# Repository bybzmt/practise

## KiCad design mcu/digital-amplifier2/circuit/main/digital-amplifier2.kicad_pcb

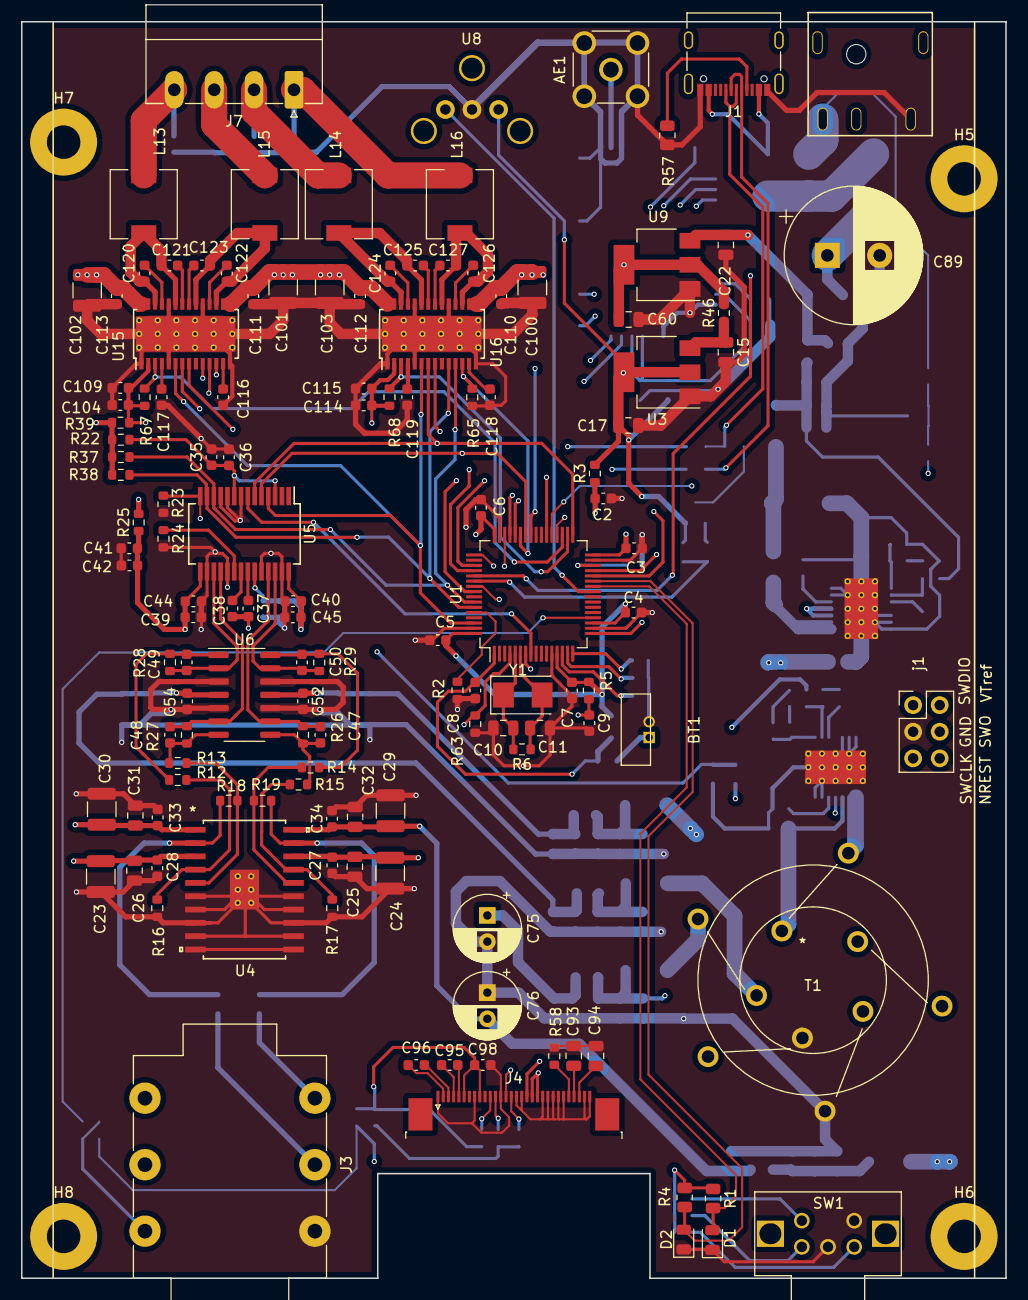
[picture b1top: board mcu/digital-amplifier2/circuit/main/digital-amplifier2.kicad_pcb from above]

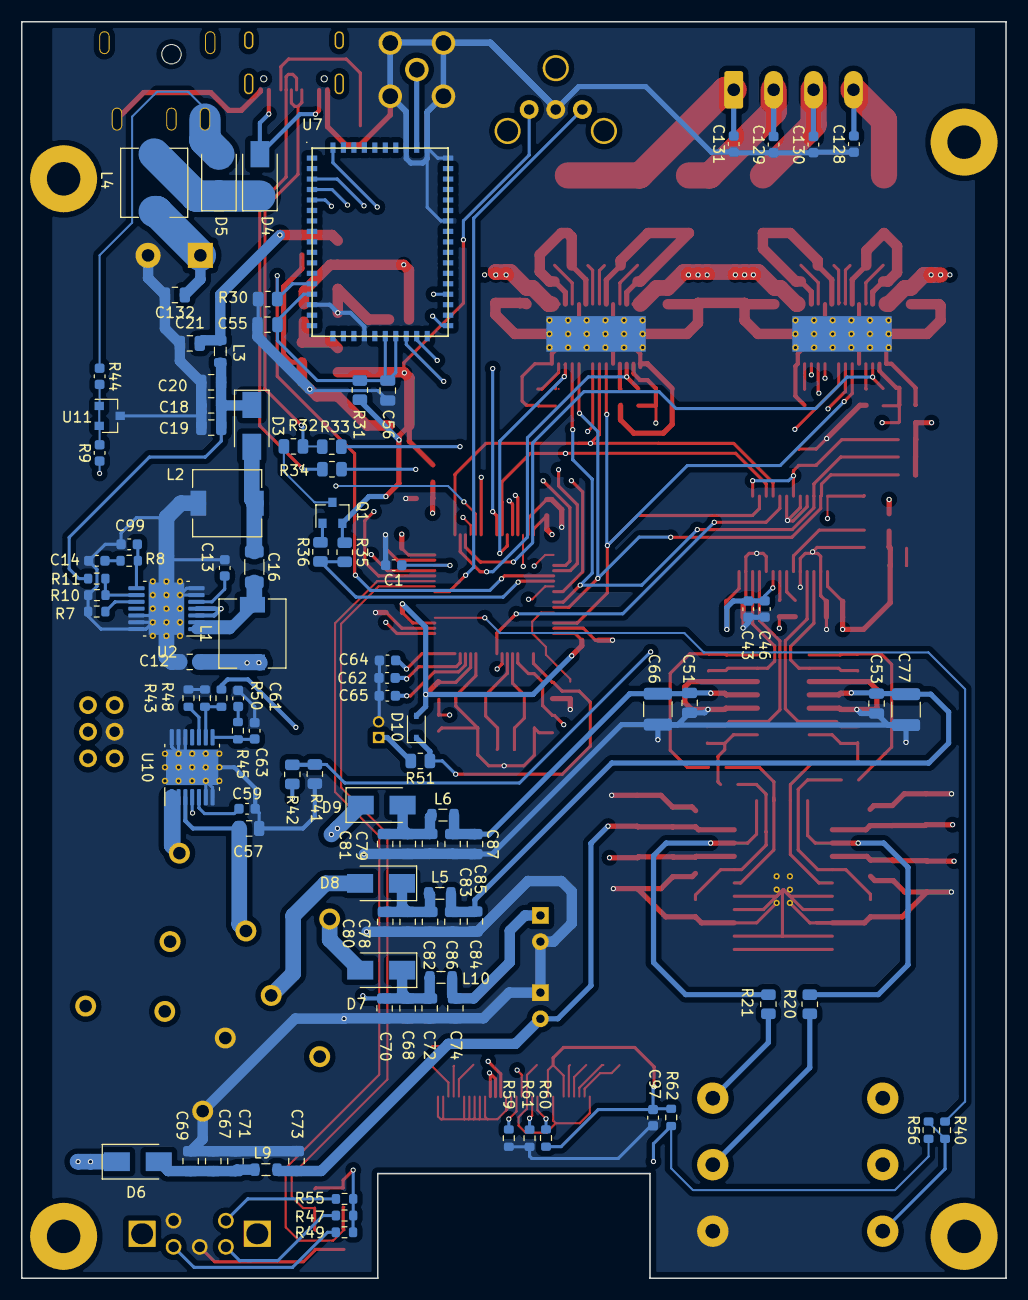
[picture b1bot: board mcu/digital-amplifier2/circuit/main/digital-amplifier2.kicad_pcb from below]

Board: 4 copper layers, 94.0 x 120.0 mm, 237 parts (101 on the bottom side), 140 nets.

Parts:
AE1: Antenna_Shield; SMA_Molex_73251-2200_Horizontal
BT1: MS621FE-FL11E
C1, C104, C114: 4.7uf; C_0603_1608Metric
C2, C35, C39, C41, C43, C45, C97: 10uf; C_0603_1608Metric
C3, C4, C5, C6, C7, C8, C9, C14, C27, C28, C33, C34, C36, C40, C42, C44, C46, C52, C54, C61, C62, C64, C65, C98, C109, C110, C111, C112, C113, C115: 100nf; C_0603_1608Metric
C10, C11: 12pf; C_0805_2012Metric
C12, C15, C25, C26, C31, C32, C51, C53, C56, C57, C93, C94, C132: 10uf; C_0805_2012Metric
C13, C59: 47nf; C_0603_1608Metric
C16: 2.2uf; C_1206_3216Metric
C17, C60: 1uf; C_0805_2012Metric
C18, C19, C21, C22, C55, C67, C68, C69, C70, C73, C74, C78, C79, C80, C81, C84, C85, C86, C87: 22uf; C_0805_2012Metric
C20, C71, C72, C82, C83: 100nf; C_0805_2012Metric
C23, C24, C29, C30, C66, C77, C100, C101, C102, C103: 47uf; C_1210_3225Metric
C37, C38: 47uf; C_0603_1608Metric
C47, C48, C49, C50: 2.7nf; C_0603_1608Metric
C63, C99: NC; C_0603_1608Metric
C75, C76: 220uf; CP_Radial_D6.3mm_P2.50mm
C89: 2200uf; CP_Radial_D13.0mm_P5.00mm
C95, C96, C116, C117, C118, C119: 1uf; C_0603_1608Metric
C120, C121, C122, C123, C124, C125, C126, C127: 220nf; C_0603_1608Metric
C128, C129, C130, C131: 680nf; C_0603_1608Metric
D1: led1; LED_0805_2012Metric
D2: led2; LED_0805_2012Metric
D3, D4, D5, D6, D7, D8, D9: ss34; D_SMA
D10: SD103AWS; D_SOD-323
H5, H6, H7, H8: m3; MountingHole_3.2mm_M3_Pad
J1: USB_C_Receptacle_USB2.0; USB_C_Receptacle_Palconn_UTC16-G
J2: Barrel_Jack_Switch; DC-044A_5.5-2.1
J3: AudioJack3_Switch; Jack_6.35mm_Neutrik_NMJ6HFD2-AU_Horizontal
J4: 0.96_oled; TE_3-1734839-0_1x30-1MP_P0.5mm_Horizontal
J7: PW_OUT; PhoenixContact_MC_1,5_4-G-3.81_1x04_P3.81mm_Horizontal
L1, L2: 22uh / 0630; L_6.3x6.3_H3
L3, L5, L6, L9, L10: 2.2uh / 0805; L_0805_2012Metric
L4: 4.7uh / 0630; L_6.3x6.3_H3
L13, L14, L15, L16: 10uh; L_6.3x6.3_H3
Q1: s8550; SOT-23
R1, R4, R30, R41, R42: 9.53k; R_0805_2012Metric
R2: 9.53kΩ; R_0603_1608Metric
R3, R22, R25, R39, R46, R62: 0Ω; R_0603_1608Metric
R5, R23, R59, R60, R61, R63, R65: 9.53k; R_0603_1608Metric
R6: 1mΩ; R_0603_1608Metric
R7, R43: 43k; R_0603_1608Metric
R8, R45: 2.37k; R_0603_1608Metric
R9, R44: 10k; C_0603_1608Metric
R10, R12, R13, R14, R15, R16, R17, R18, R19, R26, R27, R28, R29, R48: 1k; R_0603_1608Metric
R11: 5k; R_0603_1608Metric
R20, R21: 39.2Ω; R_0805_2012Metric
R24, R40, R47, R49, R55, R56: 10k; R_0603_1608Metric
R31: 0; R_0805_2012Metric
R32: 1.5k; R_0805_2012Metric
R33, R34: 12Ω; R_0805_2012Metric
R35: 22k; R_0805_2012Metric
R36, R57: 5.1k; R_0805_2012Metric
R37, R38: 4.7k; R_0603_1608Metric
R50: 11k; R_0603_1608Metric
R51: 1k; R_0805_2012Metric
R58: 760k; R_0603_1608Metric
R67: 15k; R_0603_1608Metric
R68: 47k; R_0603_1608Metric
SW1: ec11; ec11_horizontal
T1: Transformer_diy_02; Transformer_10p_22x14
U1: STM32F446RETx; LQFP-64_10x10mm_P0.5mm
U2, U10: TPS55340; HTSSOP-14-1EP_4.4x5mm_P0.65mm_EP3.4x5mm_Mask3x3.1mm_Thermal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
U3: AMS1117-3.3; SOT-223-3_TabPin2
U4: TPA6120A2; TPA6120A2DWP
U5: PCM1792A; SSOP-28_5.3x10.2mm_P0.65mm
U6: OPA4134; SOIC-14_3.9x8.7mm_P1.27mm
U7: SJR-BTM331
U8: DLT11H0; spdif-DLT11H0
U9: AMS1117-5.0; SOT-223-3_TabPin2
U11: TL431DBZ; SOT-23
U15, U16: tas5805m; HTSSOP-28-1EP_4.4x9.7mm_P0.65mm_EP3.4x9.5mm_ThermalVias
Y1: 5032 8m; Crystal_SMD_5032-2Pin_5.0x3.2mm
j1: swd_pcb_2.54

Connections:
+2V5: R9.2, R44.2, U11.1, U11.2
+3.3VDAC: C35.1, C36.1, R22.1, U5.3, U5.9
+3V3: C17.1, Q1.2, R1.1, R3.2, R4.1, R22.2, R31.2, R35.1, R37.1, R38.1, R39.2, R47.1, R49.1, R55.1, R56.1, R62.2, U3.2, U8.3
+5V: C60.1, R25.2, R46.2, U9.2
+7.5V: C18.1, C19.1, C20.1, D3.1, L3.1, R11.1
+8V: C53.1, C54.1, C77.1, C84.1, C86.1, L5.2, U6.4
+15V: C23.1, C24.1, C25.1, C26.1, C27.1, C28.1, C74.1, C75.1, L10.2, U4.3, U4.18
-8V: C51.1, C52.1, C66.1, C85.1, C87.1, L6.2, U6.11
-15V: C29.1, C30.1, C31.1, C32.1, C33.1, C34.1, C73.1, C76.2, L9.2, U4.1, U4.20
/5805_en: R65.1, U1.43, U15.12, U16.12
/BT_connected: U1.41, U7.28
/BT_en: R30.1, U1.53, U7.13
/BT_next: U1.51, U7.25
/BT_play: U1.52, U7.31
/BT_prev: U1.56, U7.26
/BT_spdif: U1.38, U7.54
/Bluetooth/vdd_x: C55.1, C56.1, R31.1, U7.14, U7.23, U7.24
/I2C_SCL: J4.18, R37.2, U1.58, U5.12, U15.11, U16.11
/I2C_SDA: J4.19, J4.20, R38.2, U1.59, U5.13, U15.10, U16.10
/LOUT: J3.T, R21.1
/OPA4134/INA: C49.2, R28.2, U5.17, U6.2
/OPA4134/INB: C48.2, R27.2, U5.18, U6.6
/OPA4134/INC: C47.2, R26.2, U5.25, U6.9
/OPA4134/IND: C50.2, R29.2, U5.26, U6.13
/OPA4134/OUTC: C47.1, R15.2, R26.1, U6.8
/OPA4134/OUTD: C50.1, R14.2, R29.1, U6.14
/PCM1792/vdd2: C37.2, C38.2, C39.1, C40.1, C41.1, C42.1, C43.1, C44.1, C45.1, C46.1, R25.1, U5.15, U5.23, U5.28
/ROUT: J3.R, R20.1
/SAI_FS: U1.62, U5.4, U15.6, U16.6
/SAI_FS_A: U1.17, U7.4
/SAI_MCK: U1.8, U5.7
/SAI_SCK: U1.33, U5.6, U15.7, U16.7
/SAI_SCK_A: U1.29, U7.5
/SAI_SD: U1.42, U5.5, U15.8, U16.8
/SAI_SD_A: U1.28, U7.3
/SPDIF_RX: U1.25, U8.1
/TAS5805M/dvdd1: C104.1, C109.1, C114.1, C115.1, R39.1, R67.2, R68.2, U15.2, U16.2
/TPA6120A2/LIN+: C49.1, R12.2, R28.1, U6.1
/TPA6120A2/LIN-: C48.1, R13.2, R27.1, U6.7
/USB_DM: R34.1, U1.44
/USB_DP: R33.1, U1.45
/USB_EN: R35.2, R36.1, U1.54
/adr1: R67.1, U1.35, U15.3
/adr2: R68.1, U1.34, U16.3
/connector/cc1: J1.A5, R57.2
/connector/d+: J1.A6, J1.B6, R32.2, R33.2
/connector/v24: D5.2, J2.1, R44.1
/connector/vcc1: D4.1, D5.1, L4.1
/ec11_a: C62.1, R47.2, SW1.A, U1.15
/ec11_b: C64.1, R49.2, SW1.B, U1.16
/ec11_sw: C65.1, R55.2, SW1.S1, U1.14
/hp_en: R23.2, R41.1, R42.2, U1.36, U5.14
/hp_power/FB1: C68.1, C70.1, C72.1, D7.1, L10.1, R50.1
/hp_power/enx: R42.1, U10.4
/hp_power/out2+: D8.2, T1.8, T1.9
/hp_power/out2-: D9.1, T1.4, T1.5
/hp_power/out+: D7.2, T1.10
/hp_power/out-: D6.1, T1.3
/hp_power/sw: T1.2, U10.1, U10.2
/jack_in: R40.1, U1.20
/nrst: C9.1, R5.2, U1.7, j1.6
/oled_096/A0: J4.15, R59.2
/oled_096/BS1: J4.11, R60.2
/oled_096/BS2: J4.12, R61.2
/oled_096/C1N: C96.2, J4.2
/oled_096/C1P: C96.1, J4.3
/oled_096/C2N: C95.2, J4.5
/oled_096/C2P: C95.1, J4.4
/oled_096/IREF: J4.26, R58.2
/oled_096/VBAT: C97.1, C98.1, J4.6, J4.9, R60.1, R62.1
/oled_096/VCCMH: C93.2, J4.27
/oled_096/VCCx: C94.2, J4.28
/oled_en: J4.14, R63.1, U1.4
/out_a+: C128.2, J7.4, L13.1
/out_a-: C130.2, J7.3, L15.1
/out_b+: C129.2, J7.2, L14.1
/out_b-: C131.2, J7.1, L16.1
/stm32/BOOT: R2.1, U1.60
/stm32/OSC_IN: C10.1, R6.2, U1.5, Y1.1
/stm32/OSC_OUT: C11.1, R6.1, U1.6, Y1.2
/stm32/VCAP: C1.1, U1.30
/stm32/led1: D1.2, R1.2, U1.26
/stm32/led2: D2.2, R4.2, U1.27
/stm32/v24: R9.1, U1.37
/stm32/vbat: C8.1, D10.1, R51.1, U1.1
/stm32/vdd1: C2.1, C3.1, C4.1, C5.1, C6.1, C7.1, D10.2, R3.1, R5.1, U1.13, U1.19, U1.32, U1.48, U1.64
/swclk: U1.49, j1.5
/swdio: U1.46, j1.1
/swo_tdo: U1.55, j1.4
GND: AE1.2, BT1.2, C1.2, C2.2, C3.2, C4.2, C5.2, C6.2, C7.2, C8.2, C9.2, C10.2, C11.2, C12.2, C13.2, C14.2, C15.2, C17.2, C18.2, C19.2, C20.2, C21.2, C22.2, C23.2, C24.2, C25.2, C26.2, C27.2, C28.2, C29.2, C30.2, C31.2, C32.2, C33.2, C34.2, C35.2, C36.2, C39.2, C40.2, C41.2, C42.2, C43.2, C44.2, C45.2, C46.2, C51.2, C52.2, C53.2, C54.2, C55.2, C56.2, C57.2, C59.2, C60.2, C61.2, C62.2, C63.2, C64.2, C65.2, C66.2, C67.2, C68.2, C69.2, C70.2, C71.2, C72.2, C73.2, C74.2, C75.2, C76.1, C77.2, C78.2, C79.2, C80.2, C81.2, C82.2, C83.2, C84.2, C85.2, C86.2, C87.2, C89.2, C93.1, C94.1, C97.2, C98.2, C99.2, C100.2, C101.2, C102.2, C103.2, C104.2, C109.2, C110.2, C111.2, C112.2, C113.2, C114.2, C115.2, C116.2, C117.2, C118.2, C119.2, C128.1, C129.1, C130.1, C131.1, C132.2, D1.1, D2.1, J1.A1, J1.A12, J1.B1, J1.B12, J2.2, J3.S, J4.1, J4.8, J4.13, J4.16, J4.17, J4.21, J4.22, J4.23, J4.24, J4.25, J4.29, J4.30, L2.2, R2.2, R7.2, R10.2, R16.2, R17.2, R23.1, R24.2, R30.2, R41.2, R43.2, R48.2, R57.1, R58.1, R59.1, R61.1, R63.2, R65.2, SW1.C, SW1.S2, T1.6, T1.7, U1.12, U1.18, U1.31, U1.47, U1.63, U2.6, U2.7, U2.12, U2.13, U2.14, U2.15, U3.1, U4.6, U4.7, U4.8, U4.9, U4.10, U4.11, U4.12, U4.13, U4.14, U4.15, U4.21, U5.8, U5.10, U5.11, U5.16, U5.19, U5.24, U5.27, U6.3, U6.5, U6.10, U6.12, U7.15, U7.21, U7.38, U7.44, U7.45, U7.47, U8.2, U9.1, U10.6, U10.7, U10.12, U10.13, U10.14, U10.15, U11.3, U15.1, U15.5, U15.14, U15.19, U15.24, U15.29, U16.1, U16.5, U16.14, U16.19, U16.24, U16.29, j1.3
unnamed: AE1.1, U7.46
unnamed: BT1.1, R51.2
unnamed: C13.1, U2.5
unnamed: C14.1, R8.2
unnamed: C15.1, R46.1, U3.3
unnamed: C16.1, D3.2, L2.1
unnamed: C16.2, L1.2, U2.1, U2.2
unnamed: C21.1, C22.1, L3.2, U9.3
unnamed: C37.1, U5.22
unnamed: C38.1, U5.21
unnamed: C59.1, U10.5
unnamed: C61.1, R45.2
unnamed: C63.1, R45.1, U10.8
unnamed: C67.1, C69.1, C71.1, D6.2, L9.1
unnamed: C78.1, C80.1, C82.1, D8.1, L5.1
unnamed: C79.1, C81.1, C83.1, D9.2, L6.1
unnamed: C99.1, R8.1, U2.8
unnamed: C116.1, U15.13
unnamed: C117.1, U15.4
unnamed: C118.1, U16.13
unnamed: C119.1, U16.4
unnamed: C120.1, C121.1, L13.2, U15.23, U15.26
unnamed: C120.2, U15.25
unnamed: C121.2, U15.22
unnamed: C122.1, C123.1, L15.2, U15.17, U15.20
unnamed: C122.2, U15.18
unnamed: C123.2, U15.21
unnamed: C124.1, C125.1, L14.2, U16.23, U16.26
unnamed: C124.2, U16.25
unnamed: C125.2, U16.22
unnamed: C126.1, C127.1, L16.2, U16.17, U16.20
unnamed: C126.2, U16.18
unnamed: C127.2, U16.21
unnamed: D4.2, J1.A4, J1.A9, J1.B4, J1.B9
unnamed: J1.A7, J1.B7, R34.2
unnamed: J3.SN, R40.2, R56.2
unnamed: Q1.1, R36.2
unnamed: Q1.3, R32.1
unnamed: R7.1, U2.10
unnamed: R10.1, R11.2, U2.9
unnamed: R12.1, R16.1, U4.4
unnamed: R13.1, R18.1, U4.5
unnamed: R14.1, R19.1, U4.16
unnamed: R15.1, R17.1, U4.17
unnamed: R18.2, R20.2, U4.2
unnamed: R19.2, R21.2, U4.19
unnamed: R24.1, U5.20
unnamed: R43.1, U10.10
unnamed: R48.1, R50.2, U10.9
VCC: C12.1, C57.1, C89.1, C100.1, C101.1, C102.1, C103.1, C110.1, C111.1, C112.1, C113.1, C132.1, L1.1, L4.2, T1.1, U2.3, U2.4, U10.3, U15.15, U15.16, U15.27, U15.28, U16.15, U16.16, U16.27, U16.28

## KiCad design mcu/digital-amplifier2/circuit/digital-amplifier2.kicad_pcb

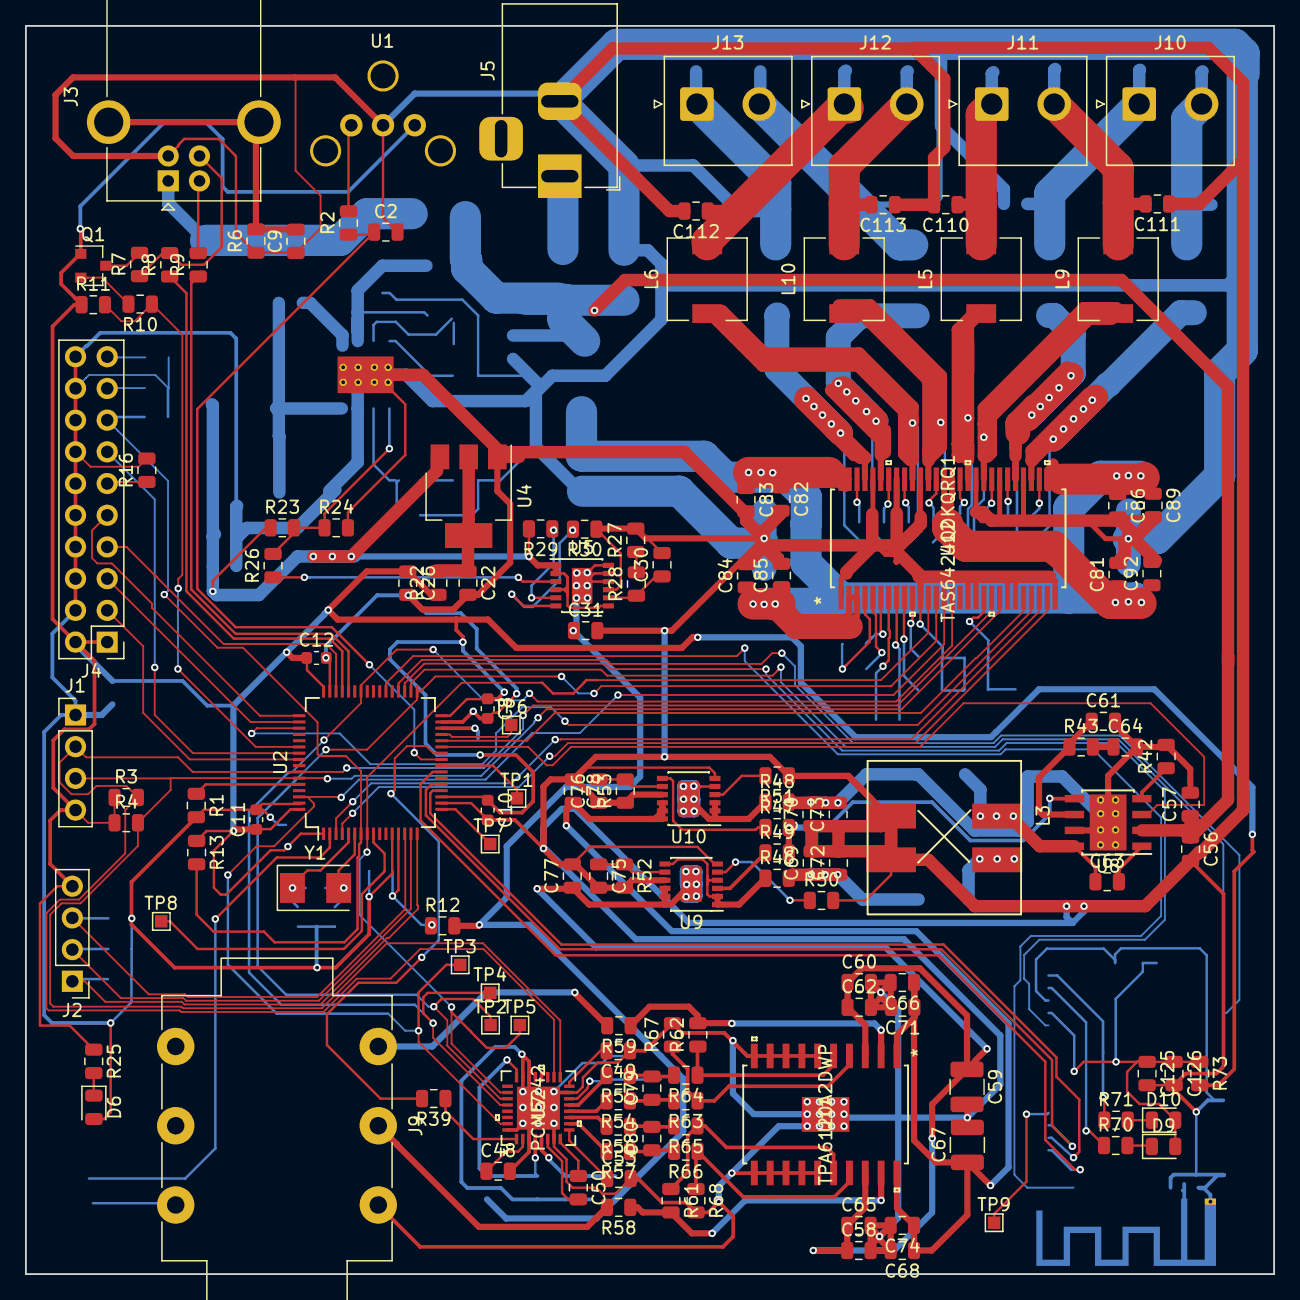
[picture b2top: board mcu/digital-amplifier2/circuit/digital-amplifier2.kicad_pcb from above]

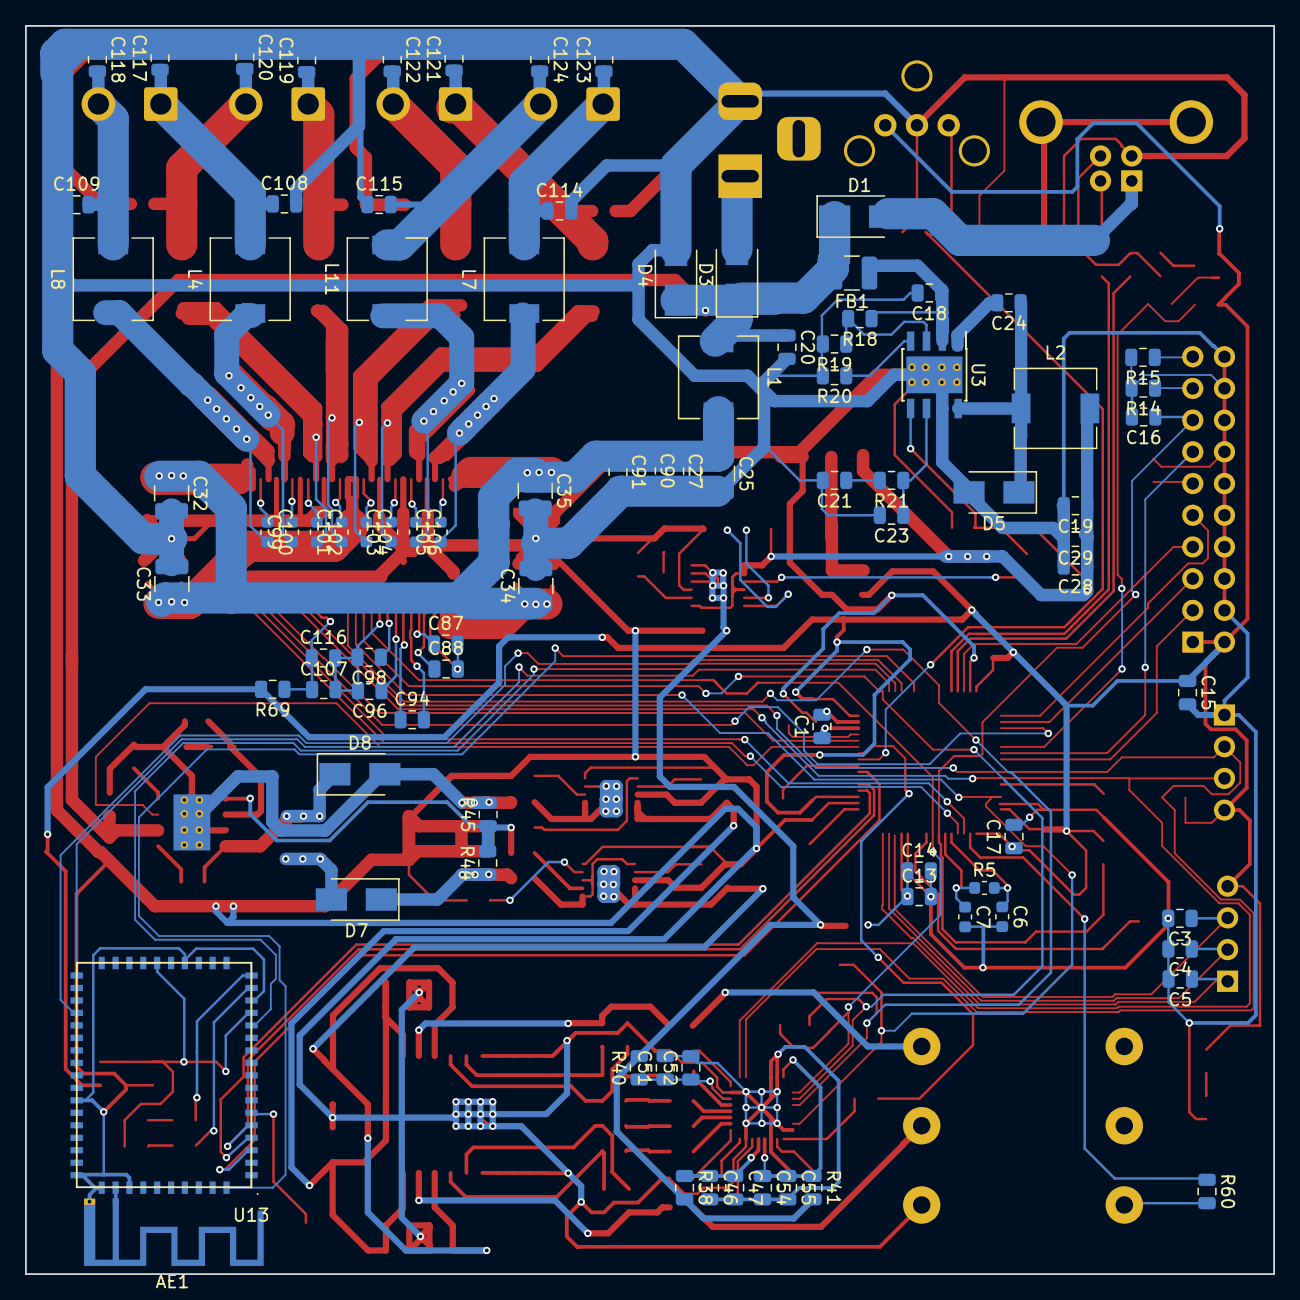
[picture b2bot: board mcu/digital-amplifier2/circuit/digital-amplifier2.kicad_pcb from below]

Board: 2 copper layers, 100.0 x 100.0 mm, 232 parts (90 on the bottom side), 158 nets.

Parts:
AE1: Antenna_Shield; Texas_SWRA117D_2.4GHz_Left
C1: 4.7uf/10v; C_0805_2012Metric
C2: 10pf; C_0805_2012Metric
C3, C4, C5, C14, C15, C16, C22, C24, C47, C52, C54, C62, C65, C71, C74, C85, C86, C91, C116: 100nf; C_0805_2012Metric
C6, C7: 12pf; C_0603_1608Metric
C8, C10, C11, C12: 100nf/10v; C_0603_1608Metric
C9: 1nF/1KV; C_0805_2012Metric
C13, C19, C26, C27, C31, C46, C51, C55, C56, C58, C60, C66, C68, C77, C78, C83, C84, C89, C92, C107, C126: 10uf; C_0805_2012Metric
C17: 100nf; R_0805_2012Metric
C18, C20, C30, C75, C76: 4.7uf; C_0805_2012Metric
C21: 6.8nf; C_0805_2012Metric
C23: 39pf; C_0805_2012Metric
C25, C32, C33, C34, C35, C59, C67: 100uf; C_1210_3225Metric
C28, C29: 47uf; C_0805_2012Metric
C48, C63: 0.1uf; C_0805_2012Metric
C49, C57, C87, C88, C90, C94, C108, C109, C110, C111, C112, C113, C114, C115: 1uf; C_0805_2012Metric
C50: 2.2uf/25v; C_0805_2012Metric
C53: 2.2uF/25V; C_0805_2012Metric
C61: 750pf; C_0805_2012Metric
C64: 5.1nf; C_0805_2012Metric
C69, C70, C72, C73, C125: 22uf; C_0805_2012Metric
C79, C80: 100pf; C_0805_2012Metric
C81, C82: 100uf; C_0805_2012Metric
C96, C98: 2.2uf; C_0805_2012Metric
C99, C100, C101, C102, C103, C104, C105, C106: 1uf; C_0603_1608Metric
C117, C118, C119, C120, C121, C122, C123, C124: 1nf; C_0805_2012Metric
D1, D7, D8: 60v 3A; D_SMA
D3, D4: 40v 5A; D_SMA
D5: B560C; D_SMA
D6: 0805; LED_0805_2012Metric
D9, D10: LED; LED_0805_2012Metric
FB1: 300 ohm @100MHz 3.1A; L_1210_3225Metric
J1: I2C_oled; PinHeader_1x04_P2.54mm_Vertical
J2: encoder; PinHeader_1x04_P2.54mm_Vertical
J3: USB_B; USB_B_OST_USB-B1HSxx_Horizontal
J4: Conn_ARM_JTAG_SWD_20; PinHeader_2x10_P2.54mm_Vertical
J5: Barrel_Jack_Switch; BarrelJack_Horizontal
J9: AudioJack3_Switch; Jack_6.35mm_Neutrik_NMJ6HFD2-AU_Horizontal
J10: Audio outA; JST_NV_B02P-NV_1x02_P5.00mm_Vertical
J11: Audio outB; JST_NV_B02P-NV_1x02_P5.00mm_Vertical
J12: Audio outC; JST_NV_B02P-NV_1x02_P5.00mm_Vertical
J13: Audio outD; JST_NV_B02P-NV_1x02_P5.00mm_Vertical
L1: 4.7uh 9.7A; L_6.3x6.3_H3
L2: 8.2uh; L_6.3x6.3_H3
L3: 150uh; MSD1278
L4, L5, L6, L7, L8, L9, L10, L11: 3.3uh; L_6.3x6.3_H3
Q1: S8550; SOT-23
R1: 9.53kΩ; R_0805_2012Metric
R2: 49.9Ω; R_0805_2012Metric
R3, R4: 4.7k; R_0805_2012Metric
R5: 1mΩ; R_0603_1608Metric
R6: 1m; R_0805_2012Metric
R7: 1.5k; R_0805_2012Metric
R8, R9: 12Ω; R_0805_2012Metric
R10: 5.1k; R_0805_2012Metric
R11, R13: 22k; R_0805_2012Metric
R12, R22, R28, R30, R38, R40, R41, R46, R48, R69, R73: 0Ω; R_0805_2012Metric
R14, R15, R16, R39, R60: 10k; R_0805_2012Metric
R18: 523k; R_0805_2012Metric
R19: 84.5k; R_0805_2012Metric
R20: 162k; R_0805_2012Metric
R21: 13k; R_0805_2012Metric
R23: 53.6k; R_0805_2012Metric
R24: 10.2k; R_0805_2012Metric
R25: 20k; R_0805_2012Metric
R26, R47, R49: test point; R_0805_2012Metric
R27: 33.2k; R_0805_2012Metric
R29, R50, R51: 200k; R_0805_2012Metric
R42: 49.9k; R_0805_2012Metric
R43: 15.4k; R_0805_2012Metric
R44: 215k; R_0805_2012Metric
R45: 12.1k; R_0805_2012Metric
R52, R53: 150k; R_0805_2012Metric
R54, R55, R56, R57, R63, R64, R65, R66: 402Ω; R_0805_2012Metric
R58, R59: 39.2Ω; R_0805_2012Metric
R61, R62, R67, R68: 806Ω; R_0805_2012Metric
R70, R71: 1k; R_0805_2012Metric
TP1, TP2, TP3, TP4, TP5, TP6, TP7, TP8, TP9: TestPoint; TestPoint_Pad_1.0x1.0mm
U1: DLT11H0; spdif-DLT11H0
U2: STM32F446RETx; LQFP-64_10x10mm_P0.5mm
U3, U8: TPS54360DDA; TI_SO-PowerPAD-8_ThermalVias
U4: AMS1117-3.3; SOT-223-3_TabPin2
U5, U9: LT3045xMSE-1; MSOP-12-1EP_3x4mm_P0.65mm_EP1.65x2.85mm
U7: PCM5242; PCM5242RHBR
U10: LT3094xMSE; MSOP-12-1EP_3x4mm_P0.65mm_EP1.65x2.85mm
U11: TPA6120A2DWP
U12: TAS6424QDKQRQ1
U13: SJR-BTM331
Y1: 5032 8m; Crystal_SMD_5032-2Pin_5.0x3.2mm

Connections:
+3.3VA: C31.1, R12.2, R38.2, R40.2, R41.2, U5.10, U5.11, U5.12, U5.13
+3V3: C8.1, C10.1, C11.1, C12.1, C15.1, C17.1, C26.1, J1.4, J2.4, J4.1, J4.2, Q1.1, R3.1, R4.1, R11.1, R13.1, R22.1, R25.1, R69.2, R73.2, U1.3, U2.1, U2.19, U2.32, U2.48, U2.64
+15V: C58.1, C59.1, C60.1, C62.1, C65.1, C77.1, U9.10, U9.11, U9.12, U9.13, U11.3, U11.18
-15V: C66.1, C67.1, C68.1, C71.1, C74.1, C78.2, U10.10, U10.11, U10.12, U11.1, U11.20
/BT_bn: U2.36, U13.31
/BT_en: U2.35, U13.13
/BT_spdif: U2.38, U13.54
/BT_state: U2.34, U13.28
/Bluetooth/vdd: C125.1, C126.1, D9.2, D10.2, R73.1, U13.14, U13.23, U13.24
/Headphone/AVDD: C51.1, C52.1, R40.1, U7.14
/Headphone/CPVDD: C46.1, C47.1, R38.1, U7.5
/Headphone/DVDD: C54.1, C55.1, R41.1, U7.4, U7.24
/Headphone/OUTLN: R56.2, U7.11
/Headphone/OUTLP: R57.2, U7.10
/Headphone/OUTRN: R55.2, U7.13
/Headphone/OUTRP: R54.2, U7.12
/Headphone/sheet5FF9330D/LOUT: R59.1, R62.2, U11.2
/Headphone/sheet5FF9330D/ROUT: R58.1, R61.2, U11.19
/I2S1_FS: U2.20, U13.4
/I2S1_MCK: TP1.1, U2.24
/I2S1_SCK: U2.21, U13.5
/I2S1_SD: U2.23, U13.3
/SAI1_CLK: TP2.1, U2.33, U7.27, U12.13
/SAI1_FS: TP3.1, U2.62, U7.31, U12.14
/SAI1_MCK: TP5.1, U2.8, U7.26, U12.12
/SAI1_SD: TP4.1, U2.42, U7.28, U12.15
/SAI2_CLK: TP6.1, U2.29
/SAI2_FS: TP7.1, U2.17
/SAI2_SD: TP8.1, U2.9
/SCL: J1.2, R3.2, U2.58, U7.18, U12.20
/SDA: J1.3, R4.2, U2.59, U7.17, U12.21
/TAS6424/BST_1M: C100.1, U12.31
/TAS6424/BST_1P: C99.2, U12.35
/TAS6424/BST_2M: C102.1, U12.37
/TAS6424/BST_2P: C101.2, U12.41
/TAS6424/BST_3M: C104.1, U12.44
/TAS6424/BST_3P: C103.2, U12.48
/TAS6424/BST_4M: C106.1, U12.50
/TAS6424/BST_4P: C105.2, U12.54
/TAS6424/OUT_1M: C100.2, L8.1, U12.32
/TAS6424/OUT_1P: C99.1, L4.1, U12.34
/TAS6424/OUT_2M: C102.2, L9.1, U12.38
/TAS6424/OUT_2P: C101.1, L5.1, U12.40
/TAS6424/OUT_3M: C104.2, L10.1, U12.45
/TAS6424/OUT_3P: C103.1, L6.1, U12.47
/TAS6424/OUT_4M: C106.2, L11.1, U12.51
/TAS6424/OUT_4P: C105.1, L7.1, U12.53
/TAS6424/vdd: C107.1, C116.1, R69.1, U12.19
/headphone_en: U2.27, U8.3
/headphone_in: R60.1, U2.2
/headphone_mute: R39.2, U2.26
/power/powin: C18.1, FB1.1, R18.1, U3.2
/stm32/AVDD: C13.1, C14.1, R12.1, U2.13
/stm32/BOOT: R1.1, U2.60
/stm32/JTDI: J4.5, U2.50
/stm32/JTDO: J4.13, U2.55
/stm32/JTRST: J4.3, U2.56
/stm32/NRST: C16.1, J4.15, R13.2, U2.7
/stm32/OSC_IN: C6.1, R5.2, U2.5, Y1.1
/stm32/OSC_OUT: C7.1, R5.1, U2.6, Y1.2
/stm32/SPDIF_RX: C2.1, R2.1, U2.25
/stm32/SWCLK: J4.9, U2.49
/stm32/SWDIO: J4.7, U2.46
/stm32/USB_CO: R10.1, R11.2, U2.54
/stm32/USB_DM: R9.1, U2.44
/stm32/USB_DP: R8.1, U2.45
/stm32/VCAP: C1.1, U2.30
/stm32/encoder_a: C4.1, J2.2, U2.15
/stm32/encoder_b: C5.1, J2.1, U2.16
/stm32/encoder_sw: C3.1, J2.3, U2.14
/tas6424_en: U2.28, U12.24
/tas6424_fault: U2.3, U12.26
/tas6424_mute: U2.51, U12.25
/tas6424_warn: U2.4, U12.27
GND: AE1.2, C1.2, C2.2, C3.2, C4.2, C5.2, C6.2, C7.2, C8.2, C9.1, C10.2, C11.2, C12.2, C13.2, C14.2, C15.2, C16.2, C17.2, C18.2, C19.2, C20.2, C21.2, C22.2, C23.2, C25.2, C26.2, C27.2, C28.2, C29.2, C30.2, C31.2, C32.2, C33.2, C34.2, C35.2, C46.2, C47.2, C48.2, C49.1, C51.2, C52.2, C53.2, C54.2, C55.2, C56.2, C58.2, C59.2, C60.2, C62.2, C65.2, C66.2, C67.2, C68.2, C69.2, C70.1, C71.2, C72.2, C73.1, C74.2, C75.2, C76.1, C77.2, C78.1, C81.2, C82.2, C83.2, C84.2, C85.2, C86.2, C89.2, C90.2, C91.2, C92.2, C96.2, C98.2, C107.2, C108.2, C109.1, C110.2, C111.1, C112.2, C113.1, C114.2, C115.1, C116.2, C117.2, C118.1, C119.2, C120.1, C121.2, C122.1, C123.2, C124.1, C125.2, C126.2, D4.2, D5.2, D6.2, J1.1, J3.4, J4.4, J4.6, J4.8, J4.10, J4.12, J4.14, J4.16, J4.18, J4.20, J5.2, J9.S, L3.2, L3.4, R1.2, R6.1, R14.2, R15.2, R16.2, R19.2, R20.2, R24.2, R27.2, R30.1, R50.2, R51.1, R52.2, R53.1, R67.2, R68.2, U1.2, U2.12, U2.18, U2.31, U2.47, U2.63, U3.7, U3.9, U4.1, U5.9, U7.3, U7.7, U7.15, U7.22, U7.23, U7.32, U7.33, U9.6, U9.9, U10.6, U10.9, U11.6, U11.7, U11.8, U11.9, U11.10, U11.11, U11.12, U11.13, U11.14, U11.15, U11.21, U12.1, U12.11, U12.17, U12.18, U12.22, U12.23, U12.28, U12.33, U12.36, U12.39, U12.46, U12.49, U12.52, U13.15, U13.21, U13.38, U13.44, U13.45, U13.47
unnamed: AE1.1, U13.46
unnamed: C9.2, J3.5, R6.2
unnamed: C21.1, R21.2
unnamed: C22.1, R22.2, U4.2
unnamed: C23.1, R21.1, U3.6
unnamed: C24.1, D5.1, L2.1, U3.8
unnamed: C24.2, U3.1
unnamed: C30.1, R28.1, U5.8
unnamed: C48.1, U7.2
unnamed: C49.2, U7.16
unnamed: C50.1, U7.8
unnamed: C50.2, U7.6
unnamed: C53.1, U7.9
unnamed: C57.2, C61.2, C64.2, C70.2, C73.2, D8.2, R42.2, R45.2, R48.2, U8.7, U8.9
unnamed: C61.1, R43.1, U8.6
unnamed: C63.1, D8.1, L3.3, U8.8
unnamed: C63.2, U8.1
unnamed: C64.1, R43.2
unnamed: C69.1, C72.1, D7.1, R44.1, R46.2
unnamed: C75.1, R52.1, U9.8
unnamed: C76.2, R53.2, U10.8
unnamed: C79.1, R54.1, R63.2
unnamed: C79.2, R55.1, R64.2
unnamed: C80.1, R57.1, R66.2
unnamed: C80.2, R56.1, R65.2
unnamed: C87.1, U12.6
unnamed: C87.2, C88.2, U12.4
unnamed: C88.1, U12.5
unnamed: C94.1, U12.8
unnamed: C94.2, U12.7
unnamed: C96.1, U12.9
unnamed: C98.1, U12.10
unnamed: C108.1, C117.1, J10.1, L4.2
unnamed: C109.2, C118.2, J10.2, L8.2
unnamed: C110.1, C119.1, J11.1, L5.2
unnamed: C111.2, C120.2, J11.2, L9.2
unnamed: C112.1, C121.1, J12.1, L6.2
unnamed: C113.2, C122.2, J12.2, L10.2
unnamed: C114.1, C123.1, J13.1, L7.2
unnamed: C115.2, C124.2, J13.2, L11.2
unnamed: D1.2, J3.1
unnamed: D3.2, J5.1
unnamed: D6.1, R25.2
unnamed: D7.2, L3.1
unnamed: D9.1, R70.2
unnamed: D10.1, R71.2
unnamed: J3.2, R9.2
unnamed: J3.3, R7.1, R8.2
unnamed: J4.11, R16.1
unnamed: J4.17, R14.1
unnamed: J4.19, R15.1
unnamed: J9.R, R58.2
unnamed: J9.SN, R60.2
unnamed: J9.T, R59.2
unnamed: Q1.2, R10.2
unnamed: Q1.3, R7.2
unnamed: R2.2, U1.1
unnamed: R18.2, R19.1, U3.3
unnamed: R20.1, U3.4
unnamed: R23.2, R24.1, R26.2, U3.5
unnamed: R26.1, U5.3
unnamed: R27.1, R28.2
unnamed: R29.1, U5.5
unnamed: R30.2, U5.6
unnamed: R39.1, U7.1
unnamed: R42.1, U8.4
unnamed: R44.2, R45.1, R47.2, R49.2, U8.5
unnamed: R46.1, U9.1, U9.2, U9.4, U9.7
unnamed: R47.1, U10.7
unnamed: R48.1, U10.1, U10.2, U10.3, U10.5, U10.13
unnamed: R49.1, U9.3
unnamed: R50.1, U9.5
unnamed: R51.2, U10.4
unnamed: R61.1, R65.1, U11.16
unnamed: R62.1, R64.1, U11.5
unnamed: R63.1, R67.1, U11.4
unnamed: R66.1, R68.1, U11.17
unnamed: R70.1, U13.16
unnamed: R71.1, U13.17
unnamed: TP9.1, U13.6
VCC: C20.1, C56.1, C57.1, D1.1, D3.1, D4.1, FB1.2, L1.1, U8.2
VCCQ: C25.1, C27.1, C32.1, C33.1, C34.1, C35.1, C81.1, C82.1, C83.1, C84.1, C85.1, C86.1, C89.1, C90.1, C91.1, C92.1, L1.2, U12.2, U12.3, U12.29, U12.30, U12.42, U12.43, U12.55, U12.56
VDD: C19.1, C28.1, C29.1, L2.2, R23.1, R29.2, U4.3, U5.1, U5.2, U5.4, U5.7

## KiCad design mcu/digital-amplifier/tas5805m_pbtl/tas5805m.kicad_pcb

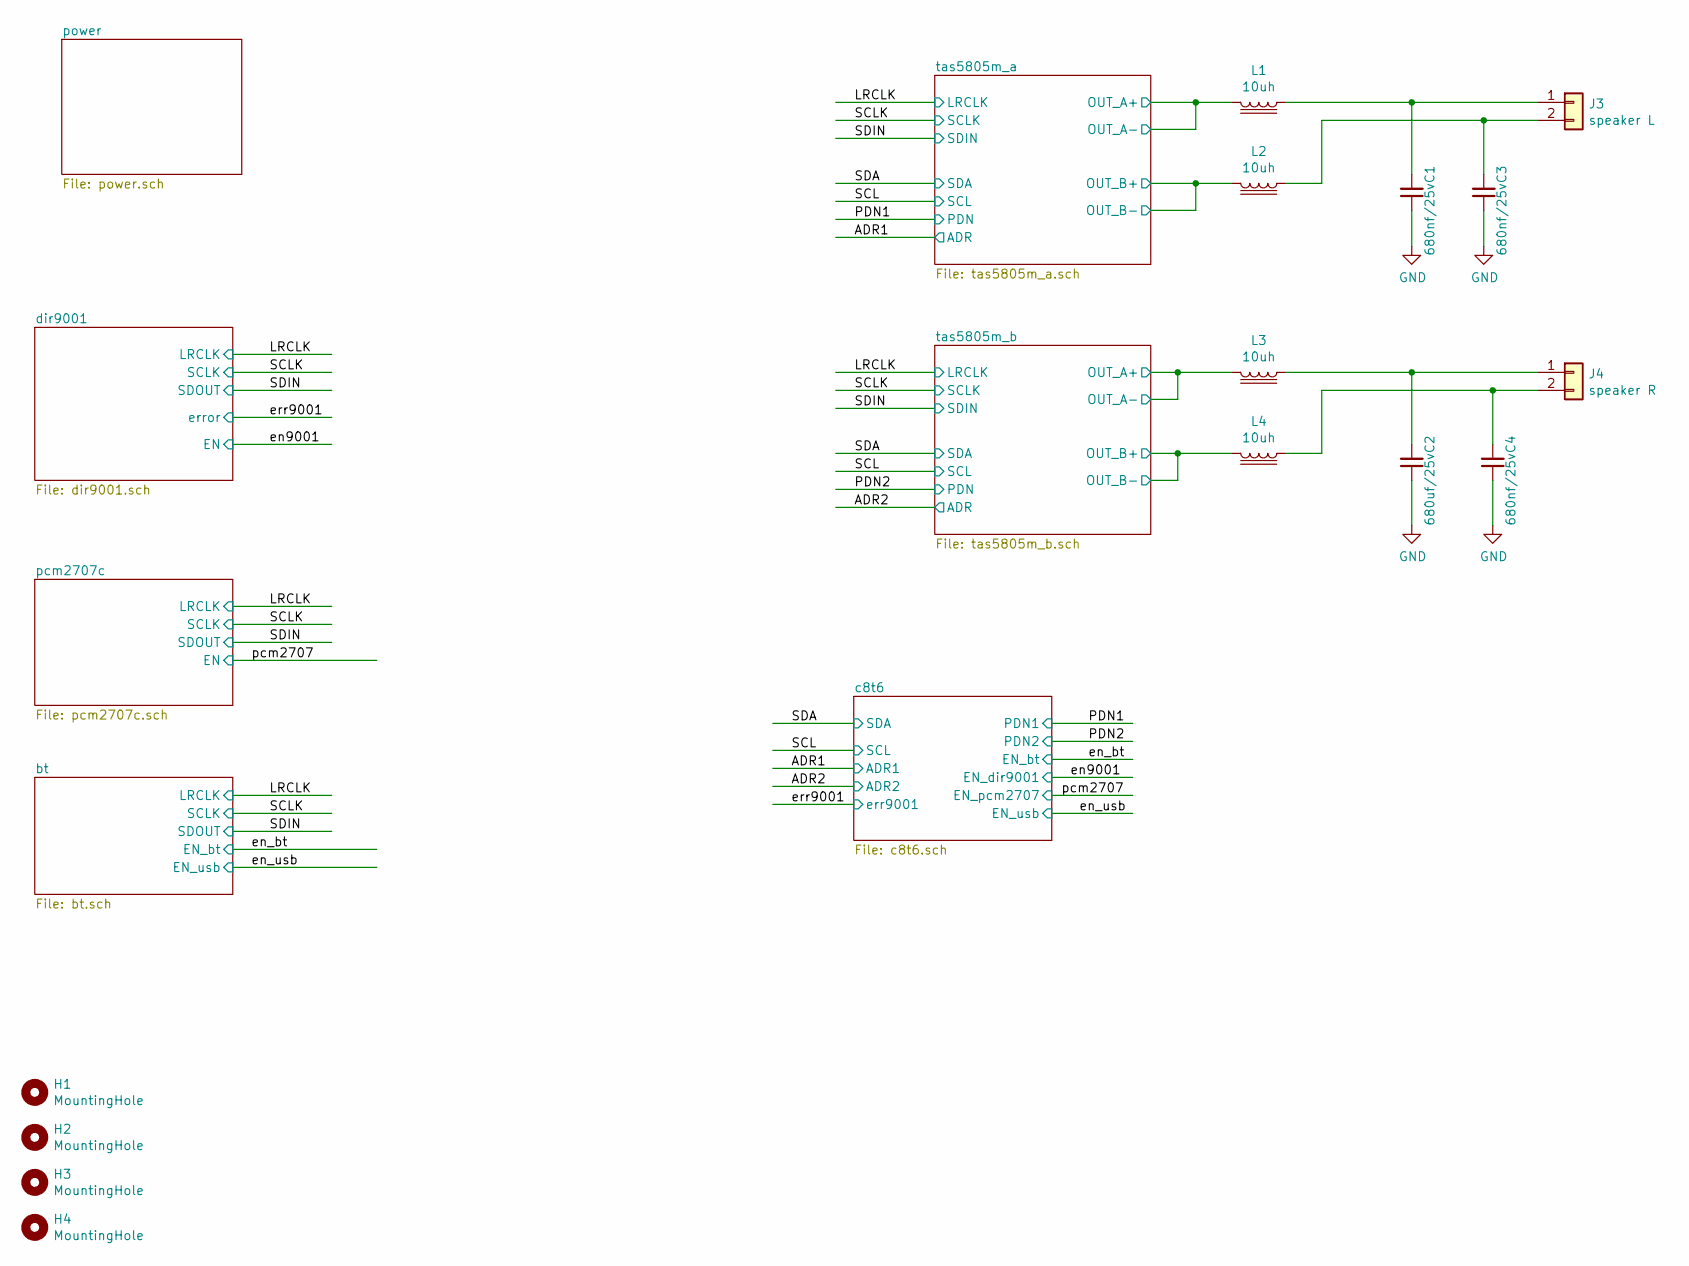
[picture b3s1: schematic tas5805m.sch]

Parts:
C1, C3, C4: 680nf/25v; C_0805_2012Metric
C2: 680uf/25v; C_0805_2012Metric
H1, H2, H3, H4: MountingHole; MountingHole_3.2mm_M3_ISO7380
J3: speaker L; kf7.62
J4: speaker R; kf7.62
L1, L2, L3, L4: 10uh; L_7.3x7.3_H4.5

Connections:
/tas5805m_a/OUT_A+: L1.2; also elsewhere on the board
/tas5805m_a/OUT_B+: L2.2; also elsewhere on the board
/tas5805m_b/OUT_A+: L3.2; also elsewhere on the board
/tas5805m_b/OUT_B+: L4.2; also elsewhere on the board
GND: C1.1, C2.1, C3.1, C4.1; also elsewhere on the board
unnamed: C1.2, J3.1, L1.1
unnamed: C2.2, J4.1, L3.1
unnamed: C3.2, J3.2, L2.1
unnamed: C4.2, J4.2, L4.1

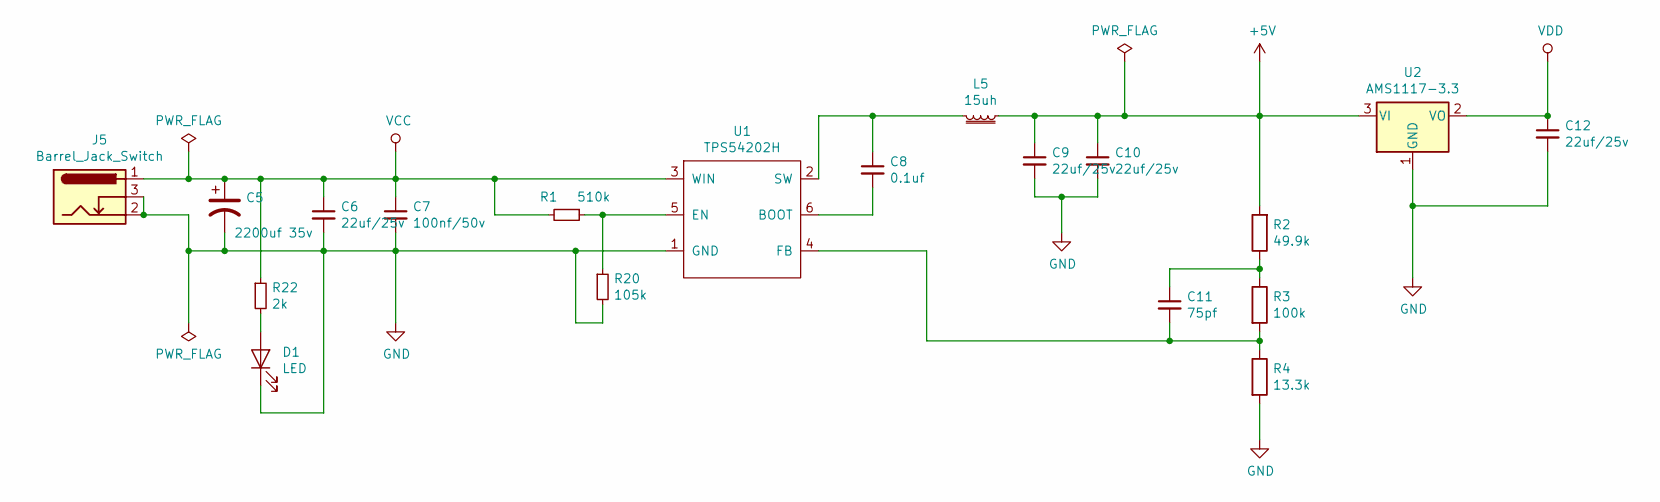
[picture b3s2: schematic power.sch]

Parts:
C5: 2200uf 35v; CP_Radial_D16.0mm_P7.50mm
C6, C9, C10, C12: 22uf/25v; C_0805_2012Metric
C7: 100nf/50v; C_0805_2012Metric
C8: 0.1uf; C_0805_2012Metric
C11: 75pf; C_0805_2012Metric
D1: LED; LED_0805_2012Metric
J5: Barrel_Jack_Switch; BarrelJack_Horizontal
L5: 15uh; L_7.3x7.3_H4.5
R1: 510k; R_0805_2012Metric
R2: 49.9k; R_0805_2012Metric
R3: 100k; R_0805_2012Metric
R4: 13.3k; R_0805_2012Metric
R20: 105k; R_0805_2012Metric
R22: 2k; R_0805_2012Metric
U1: TPS54202H; SOT-23-6
U2: AMS1117-3.3; SOT-223-3_TabPin2

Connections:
+5V: C9.1, C10.1, L5.1, R2.2, U2.3 (VI); also elsewhere on the board
GND: C5.2, C6.2, C7.2, C9.2, C10.2, C12.2, D1.1 (K), J5.2, J5.3, R4.2, R20.2, U1.1 (GND), U2.1 (GND); also elsewhere on the board
unnamed: C8.1, L5.2, U1.2 (SW)
unnamed: C8.2, U1.6 (BOOT)
unnamed: C11.1, R2.1, R3.1
unnamed: C11.2, R3.2, R4.1, U1.4 (FB)
unnamed: D1.2 (A), R22.2
unnamed: R1.1, R20.1, U1.5 (EN)
VCC: C5.1, C6.1, C7.1, J5.1, R1.2, R22.1, U1.3 (WIN); also elsewhere on the board
VDD: C12.1, U2.2 (VO); also elsewhere on the board

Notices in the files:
parts and their libraries:
Copyright 2016 Accelerated Designs. All rights reserved.
